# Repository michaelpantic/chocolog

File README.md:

# chocolog

Folder description:
--------------------

- src: All arduino source files
- libraries: All external libraries to be copied in users library folder
- libraries_root: Libraries that need to be exchanged in /usr/share/arduino/libraries. Just the LCD Library that supports shift registers out of the box.

Used Hardware:
--------------

- Arduno Uno
- Sparkfun micro SD-Shield
- Basic 16x2 Character LCD 5V and Shift Register 74HC595 (connected using SPI)
- DS1307RTC Clock break out (connected using I2C)
- 10x DS18B20 Temperature Sensor (Connected using single pin)

Bill of material:
-----------------
- Real Time Clock Module x1
- Audio Cable TRRS - 18" (pigtail) x3
- Shift Register 8-Bit - 74HC595 x2
- Trimpot 10K with Knob x1
- Resistor Kit - 1/4W (500 total) x1
- Audio Jack - 3.5mm (Panel Mount) x3
- Metal Pushbutton - Momentary (16mm, Red) x1
- Metal Pushbutton - Momentary (16mm, Blue) x1
- microSD Shield x1
- Arduino Uno - R3 x1
- Basic 16x2 Character LCD - White on Black 5V x1
- Hook-up Wire - Black (22 AWG) x1
- Heat Shrink - Black 5' x 1/4" x1
- Arduino Stackable Header - 8 Pin x3
- Arduino Stackable Header - 6 Pin x2
- Screw - Phillips Head (1/2", 4-40, 10 pack) x1
- Nut - Metal (4-40, 10 pack) x1
- DC Barrel Jack - Panel Mount x1
- Standoff - Nylon (4-40; 3/8"; 10 pack) x1
- Enclosure - Aluminum (120x95x35mm) x1
- Temperature Sensor - Waterproof (DS18B20) x10
- Wall Adapter Power Supply - 5V DC 2A (Barrel Jack) x1

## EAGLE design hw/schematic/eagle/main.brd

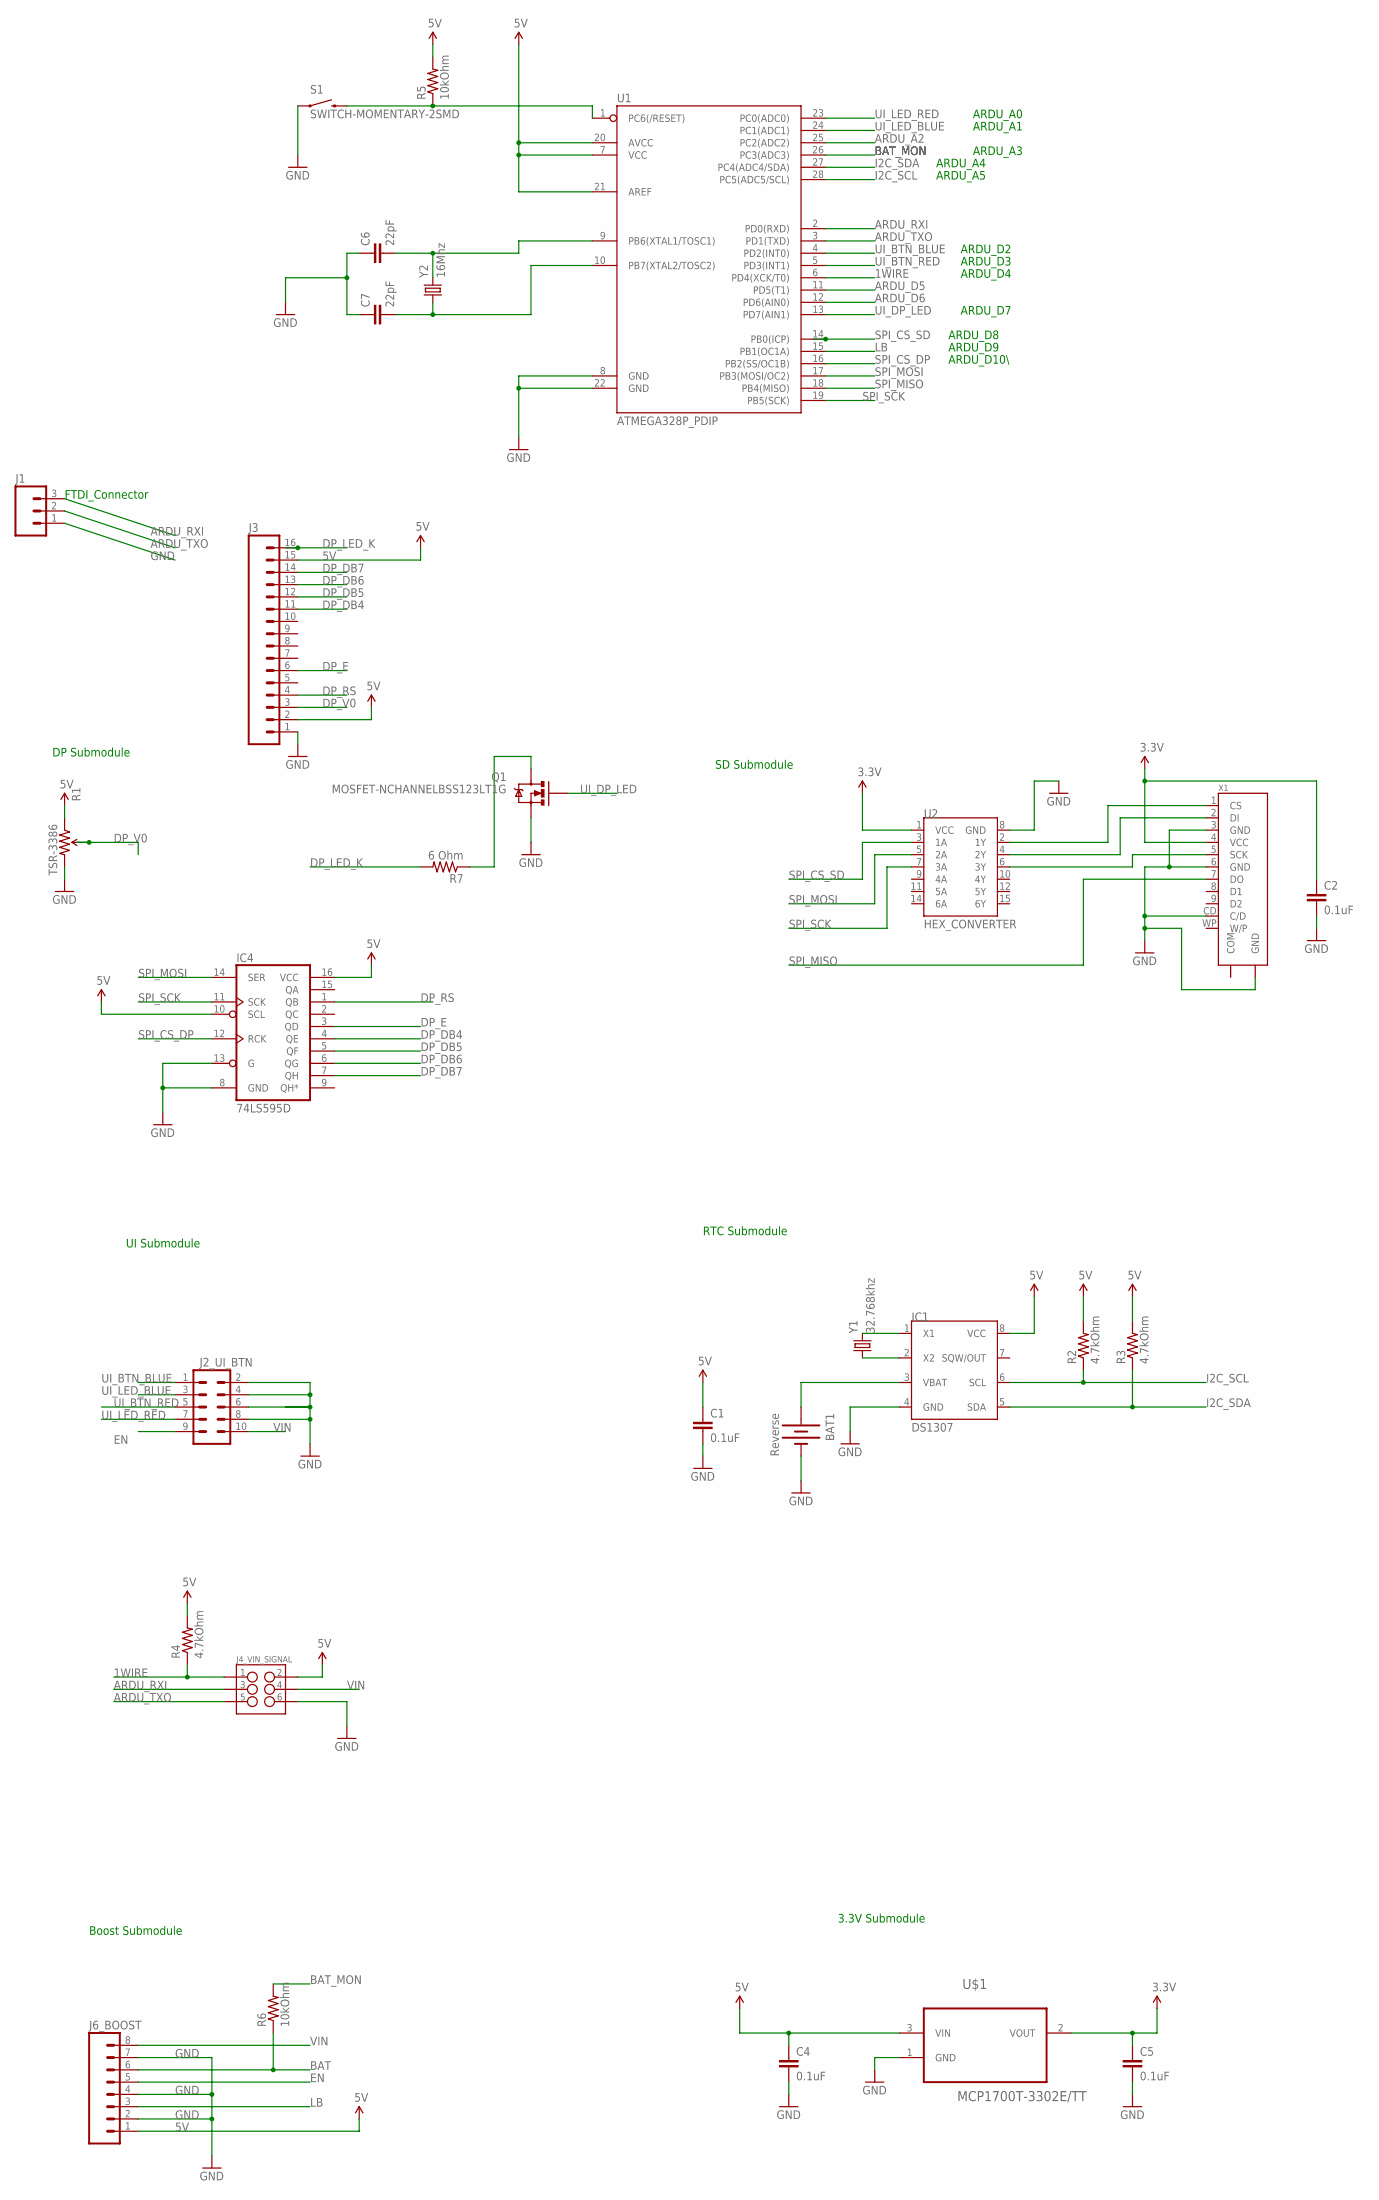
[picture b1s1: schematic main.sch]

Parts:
BAT1: Reverse; BATTCOM_20MM_PTH
C1, C2, C4, C5: 0.1uF; 1206
C6, C7: 22pF; 1206
IC1: DS1307; SOIC-8
IC4: 74LS595D; SO16
J1: M03LOCK; 1X03_LOCK
J2_UI_BTN: M05X2SHD; 2X5-SHROUDED
J3: M16PTH; 1X16
J4_VIN_SIGNAL: M03X2SHROUD; 2X3-SHROUDED
J6_BOOST: M08; 1X08_ROUND
Q1: MOSFET-NCHANNELBSS123LT1G; SOT23-3
R1: TSR-3386; 3386U
R2, R3, R4: 4.7kOhm; 1206
R5, R6: 10kOhm; 1206
R7: 6 Ohm; 1206
S1: SWITCH-MOMENTARY-2SMD; TACTILE-SWITCH-SMD
U1: ATMEGA328P_PDIP; DIL28-3
U2: HEX_CONVERTER; SO016
U$1: MCP1700T-3302E/TT; SOT95P237X112-3N
X1: SD-SOCKET-AVX
Y1: 32.768khz; CRYSTAL-32KHZ-SMD-MELF
Y2: 16Mhz; HC49US

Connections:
1WIRE: J4_VIN_SIGNAL.1, R4.1, U1.6 (PD4(XCK/T0))
3.3V: C2.1, C5.1, U2.1 (VCC), U$1.2 (VOUT), X1.4 (VCC)
5V: C1.1, C4.1, IC1.8 (VCC), IC4.10 (SCL), IC4.16 (VCC), J3.2, J3.15, J4_VIN_SIGNAL.2, J6_BOOST.1, R1.1 (CCW), R2.2, R3.2, R4.2, R5.2, U1.7 (VCC), U1.20 (AVCC), U1.21 (AREF), U$1.3 (VIN)
ARDU_A2: U1.25 (PC2(ADC2))
ARDU_D5: U1.11 (PD5(T1))
ARDU_D6: U1.12 (PD6(AIN0))
ARDU_RXI: J1.3, J4_VIN_SIGNAL.3, U1.2 (PD0(RXD))
ARDU_TXO: J1.2, J4_VIN_SIGNAL.5, U1.3 (PD1(TXD))
BAT: J6_BOOST.6, R6.1
BAT_MON: R6.2, U1.26 (PC3(ADC3))
DP_DB4: IC4.4 (QE), J3.11
DP_DB5: IC4.5 (QF), J3.12
DP_DB6: IC4.6 (QG), J3.13
DP_DB7: IC4.7 (QH), J3.14
DP_E: IC4.3 (QD), J3.6
DP_LED_K: J3.16, R7.2
DP_RS: IC4.1 (QB), J3.4
DP_V0: J3.3, R1.2 (WIPER)
EN: J2_UI_BTN.9, J6_BOOST.5
GND: BAT1.2 (-), C1.2, C2.2, C4.2, C5.2, C6.1, C7.1, IC1.4 (GND), IC4.8 (GND), IC4.13 (G), J1.1, J2_UI_BTN.2, J2_UI_BTN.4, J2_UI_BTN.6, J2_UI_BTN.8, J3.1, J4_VIN_SIGNAL.6, J6_BOOST.2, J6_BOOST.4, J6_BOOST.7, Q1.2 (S), R1.3 (CW), S1.1, U1.8 (GND), U1.22 (GND), U2.8 (GND), U$1.1 (GND), X1.3 (GND), X1.6 (GND), X1.CD (C/D), X1.GND@2 (GND)
I2C_SCL: IC1.6 (SCL), R2.1, U1.28 (PC5(ADC5/SCL))
I2C_SDA: IC1.5 (SDA), R3.1, U1.27 (PC4(ADC4/SDA))
LB: J6_BOOST.3, U1.15 (PB1(OC1A))
unnamed: BAT1.1 (+), IC1.3 (VBAT)
unnamed: IC1.2 (X2), Y1.X1 (1)
unnamed: IC1.1 (X1), Y1.X2 (2)
unnamed: U2.2 (1Y), X1.1 (CS)
unnamed: U2.4 (2Y), X1.2 (DI)
unnamed: U2.6 (3Y), X1.5 (SCK)
unnamed: R5.1, S1.3 (2), U1.1 (PC6(/RESET))
unnamed: Q1.3 (D), R7.1
unnamed: C6.2, U1.9 (PB6(XTAL1/TOSC1)), Y2.2
unnamed: C7.2, U1.10 (PB7(XTAL2/TOSC2)), Y2.1
SPI_CS_DP: IC4.12 (RCK), U1.16 (PB2(SS/OC1B))
SPI_CS_SD: U1.14 (PB0(ICP)), U2.3 (1A)
SPI_MISO: U1.18 (PB4(MISO)), X1.7 (DO)
SPI_MOSI: IC4.14 (SER), U1.17 (PB3(MOSI/OC2)), U2.5 (2A)
SPI_SCK: IC4.11 (SCK), U1.19 (PB5(SCK)), U2.7 (3A)
UI_BTN_BLUE: J2_UI_BTN.1, U1.4 (PD2(INT0))
UI_BTN_RED: J2_UI_BTN.5, U1.5 (PD3(INT1))
UI_DP_LED: Q1.1 (G), U1.13 (PD7(AIN1))
UI_LED_BLUE: J2_UI_BTN.3, U1.24 (PC1(ADC1))
UI_LED_RED: J2_UI_BTN.7, U1.23 (PC0(ADC0))
VIN: J2_UI_BTN.10, J4_VIN_SIGNAL.4, J6_BOOST.8

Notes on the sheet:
RTC Submodule
SD Submodule
DP Submodule
UI Submodule
Boost Submodule
3.3V Submodule
ARDU_A4
ARDU_A5
ARDU_D10\
ARDU_D8
ARDU_A0
ARDU_A1
ARDU_D4
ARDU_D3
ARDU_D2
ARDU_A3
ARDU_D9
ARDU_D7
FTDI_Connector

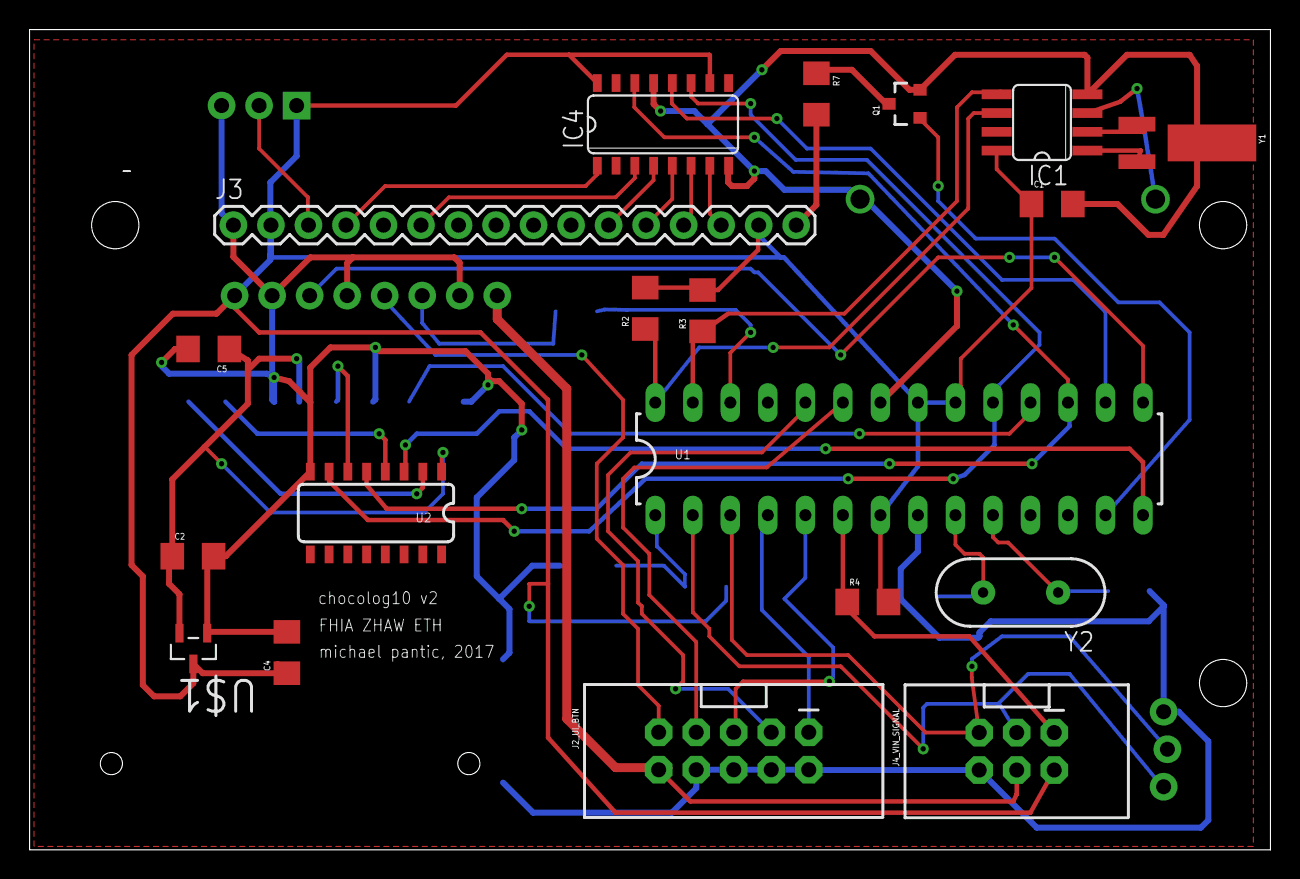
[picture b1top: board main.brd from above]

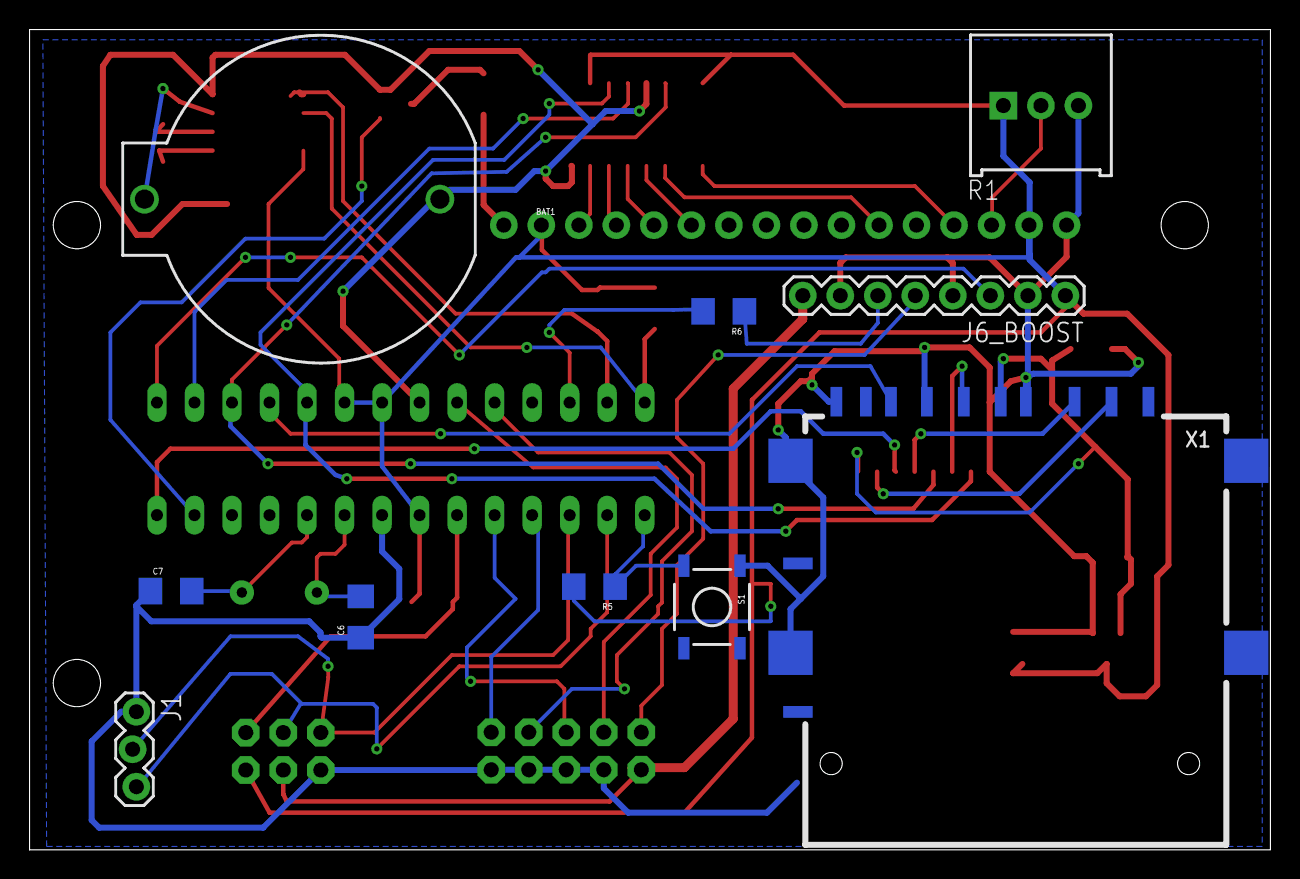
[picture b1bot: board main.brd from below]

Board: 2 copper layers, 84.0 x 55.5 mm, 29 parts (10 on the bottom side), 41 nets.

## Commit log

2016-02-25 Working version of 2014
2016-02-25 Fixed Readm
2016-02-25 Fixed folder name for arduino IDE
2017-01-02 Eagles files
2017-01-14 Schematic, Gerbers used in production
2017-01-14 First buggy implementation of energy save mode
2017-01-15 Serial number in EEPROM
2017-01-22 3df files
2017-02-26 Base code for humdity sensor
2017-02-26 Time
2017-05-14 Working DHT31 proof of concept
2017-08-27 Working humidity sensor
2017-08-27 Version Aug2017
2018-08-21 Test
2021-06-21 updated libraries, version as delivered 22-06-21

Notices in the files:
parts and their libraries:
SparkFun-DigitalIC: Licensing: Creative Commons ShareAlike 4.0 International - https://creativecommons.org/licenses/by-sa/4.0
